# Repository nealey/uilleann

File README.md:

Uilleann
=======

This is my work to model a 3D printable Uilleann Pipe full set.

I need a better name for this project.

Printing Advice
=============

Reeds
------

The Daye drones feature 3D printable reeds,
based on the laudable work of Animatorgeek.
Reeds need to simulate natural cane,
so the following print settings should be used on every reed:

Fill pattern: Aligned Rectilinear  
Fill density: 100%  
Fill angle: 90°  
Bottom solid layers: 0  
Layer height: 0.05  
Perimiters: 1  
Seam position:  Aligned (or whatever gets seams off the reed and onto the base)  
Top solid layers: 0  

Some light sanding may be required after printing.

Daye
====

Based on David Daye's Budget Drones and Penny Chanter owned by me.
David Daye has published extensive notes on how to recreate his builds
at <https://daye1.com/>, including measurements for these parts.

Rowsome
=======

This is based on the O'Flynn Leo Rewsome set,
documented at pipers.id.

http://pipers.ie/source/section/?sectionId=8 has been invaluable, providing
detailed documentation of measurements of pipes.

* [photos](https://pipers.ie/source/gallery?galleryId=115)
* [diagrams](http://pipers.ie/source/gallery?galleryId=1353)

Decorations
----------

The diagrams didn't specify exact values for every measurement,
so I took some aesthetic liberties with some parts (mostly decorative ones).

Bump-Outs
----------

I think this chanter has some extra keys that I'm not going to implement,
so I skipped a lot of the bump-out warty things on the side.

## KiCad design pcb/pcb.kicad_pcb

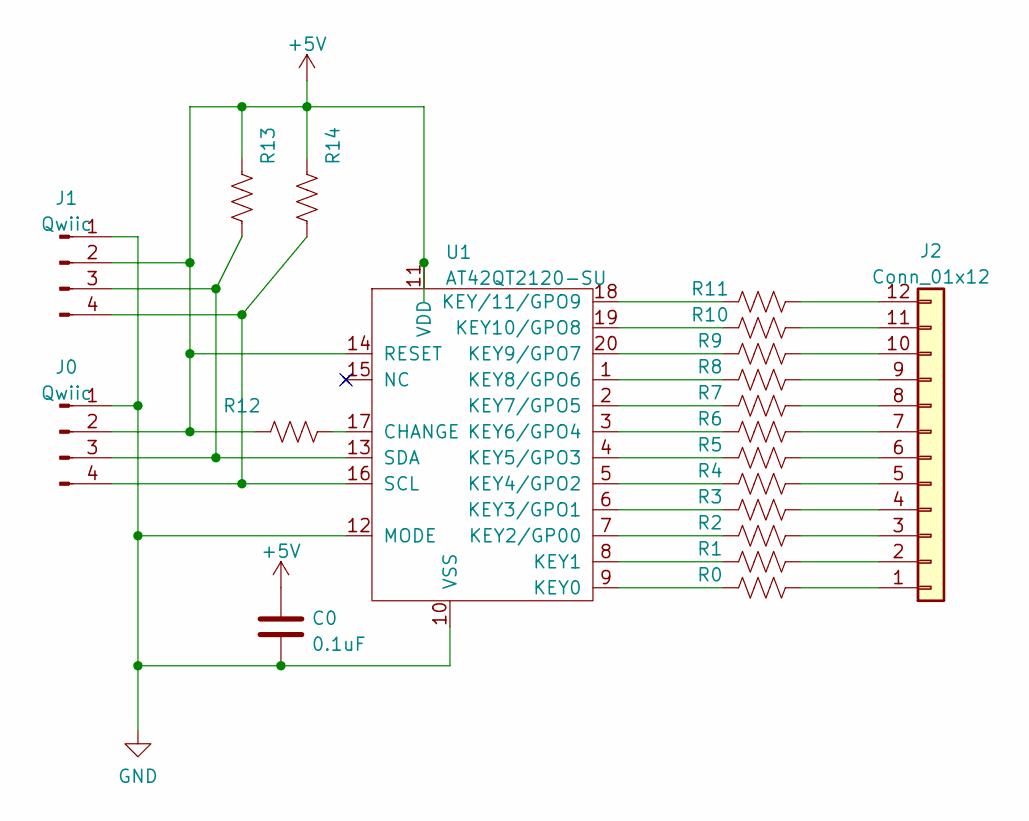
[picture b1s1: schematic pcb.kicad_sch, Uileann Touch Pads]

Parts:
C0: 0.1uF; C_0805_2012Metric_Pad1.18x1.45mm_HandSolder
J0, J1: Qwiic; JST_SH_SM04B-SRSS-TB_1x04-1MP_P1.00mm_Horizontal
J2: Conn_01x12; PinHeader_1x12_P2.54mm_Vertical
R0, R1, R2, R3, R4, R5, R6, R7, R8, R9, R10, R11: 4.7k; R_0805_2012Metric_Pad1.20x1.40mm_HandSolder
R12: 47k; R_0805_2012Metric_Pad1.20x1.40mm_HandSolder
R13, R14: 1k; R_0805_2012Metric_Pad1.20x1.40mm_HandSolder
U1: AT42QT2120-SU

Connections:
+5V: C0.1, J0.2, J1.2, R12.2, R13.2, R14.2, U1.11 (VDD), U1.14 (RESET)
GND: C0.2, J0.1, J1.1, U1.10 (VSS), U1.12 (MODE)
unnamed: J0.3, J1.3, R13.1, U1.13 (SDA)
unnamed: J0.4, J1.4, R14.1, U1.16 (SCL)
unnamed: J2.1, R0.1
unnamed: J2.2, R1.1
unnamed: J2.3, R2.1
unnamed: J2.4, R3.1
unnamed: J2.5, R4.1
unnamed: J2.6, R5.1
unnamed: J2.7, R6.1
unnamed: J2.8, R7.1
unnamed: J2.9, R8.1
unnamed: J2.10, R9.1
unnamed: J2.11, R10.1
unnamed: J2.12, R11.1
unnamed: R0.2, U1.9 (KEY0)
unnamed: R1.2, U1.8 (KEY1)
unnamed: R2.2, U1.7 (KEY2/GP00)
unnamed: R3.2, U1.6 (KEY3/GPO1)
unnamed: R4.2, U1.5 (KEY4/GPO2)
unnamed: R5.2, U1.4 (KEY5/GPO3)
unnamed: R6.2, U1.3 (KEY6/GPO4)
unnamed: R7.2, U1.2 (KEY7/GPO5)
unnamed: R8.2, U1.1 (KEY8/GPO6)
unnamed: R9.2, U1.20 (KEY9/GPO7)
unnamed: R10.2, U1.19 (KEY10/GPO8)
unnamed: R11.2, U1.18 (KEY/11/GPO9)
unnamed: R12.1, U1.17 (CHANGE)

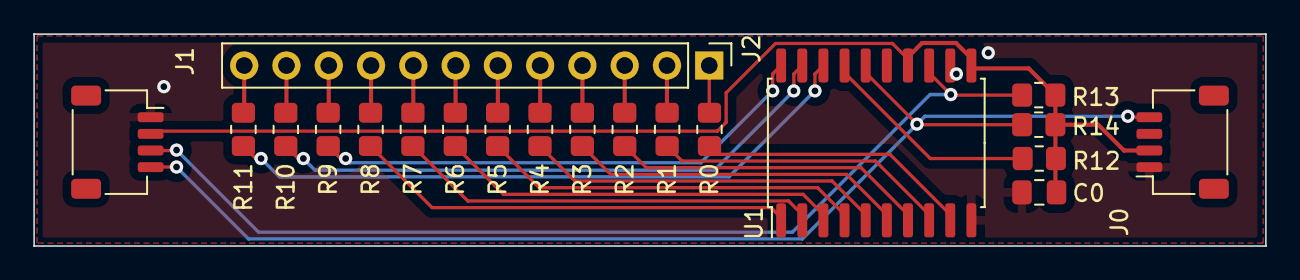
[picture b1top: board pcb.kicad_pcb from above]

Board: 2 copper layers, 74.0 x 12.7 mm, 20 parts (0 on the bottom side), 29 nets.

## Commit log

2020-10-12 Initial commit: works
2020-10-12 testing git on windows
2020-10-13 Quicker cutoff
2020-10-17 Pitch adjustment
2020-10-18 normalize adjustables
2020-10-18 "Forked F" is now the muted one
2020-10-18 finally fixed glissando!
2020-10-18 Add bag
2020-10-25 Better-defined voices, to prepare for polyphony
2020-10-25 backport missing modulated waveform class
2020-10-25 Makefile: create a uf2 file
2020-10-25 Making sound again
2020-10-26 Enable drones
2020-10-26 Detune drones slightly
2020-11-11 Working on teensy 4.0 + PAJ7620
2020-11-12 FMVoice is now a class
2020-11-12 Pipe is now a class!
2020-11-15 trying to locate source of freeze
2020-11-15 more
2020-11-23 Get it working with SGTL5000
2020-11-24 Start writing setup mode
2020-11-24 Setup menu, new Tuning class
2020-11-25 Now you can adjust pitch and intonation
2020-11-25 Make tuning.h easier to read
2020-11-26 Playing now, with a crash somewhere
2020-11-26 Working now!
2020-11-26 Sorting out glissando
2020-11-27 Glissando working again
2020-11-27 turn on white noise for debugging
2020-11-27 Fix volume adjustment
2022-04-17 v3 of button design
    It sticks more than I like, bringing back v2 elements next
2022-04-18 One last change to button before abandoning it
2022-05-01 First stab at a PCB
2022-05-01 Second stab at a PCB
2023-04-19 It lives again! Adafruit Trellis M4 Express
2023-04-20 Giving up on PCB
2023-04-20 Fix makefile
2023-04-20 Designing buttons turns out to be difficult.
2023-12-31 Remove button, bad idea
2023-12-31 check in some work on a simplified chanter
2025-01-01 Transition to a solely physical bagpipe design
2025-01-01 Done with tenor tuner parts
2025-01-02 more daye drone work, organization
2025-01-03 Add bass drone tuner
2025-01-19 try 1 at reed body
2025-01-26 Add a printable single reed!
2025-01-27 reed refinements
2025-02-01 start work on chanter reed
2025-02-19 Add penny chanter
2025-02-19 completed penny chanter
2025-02-20 Further tuning of chanter
